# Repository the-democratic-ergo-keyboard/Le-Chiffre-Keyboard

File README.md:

# Le Chiffre (ironically, "the number" in French)
The purpose of the board is to provide a platform for MX and Choc ergo (Alps support too!) in one package for when ones wrists need a break. The board supports an RGB LED strip with DI on port F0. The board is also fitted with support for run-of-the-mill .91" OLED and EC11 rotary encoder.

Great thanks goes to Jake at P3D for really making the case amazing and open sourcing his work. Check him out at P3Dstore.com

Firmware for the keyboard is available here: https://github.com/qmk/qmk_firmware/tree/master/keyboards/tominabox1/le_chiffre

This project is open sourced with the GPL-3.0 license. The license conditionally allows for commercial use, modification, distribution, patent, and private use. Please take note of the license conditions before utilizing this project. 

## PCB

# Fab files
If you just want to order PCBs, just grab these files and send them to your fab house. The pos and bom for jlcpcb are already included as well

[PCB](KiCad/Le%20Chiffre%20v2/production/gerber.zip)

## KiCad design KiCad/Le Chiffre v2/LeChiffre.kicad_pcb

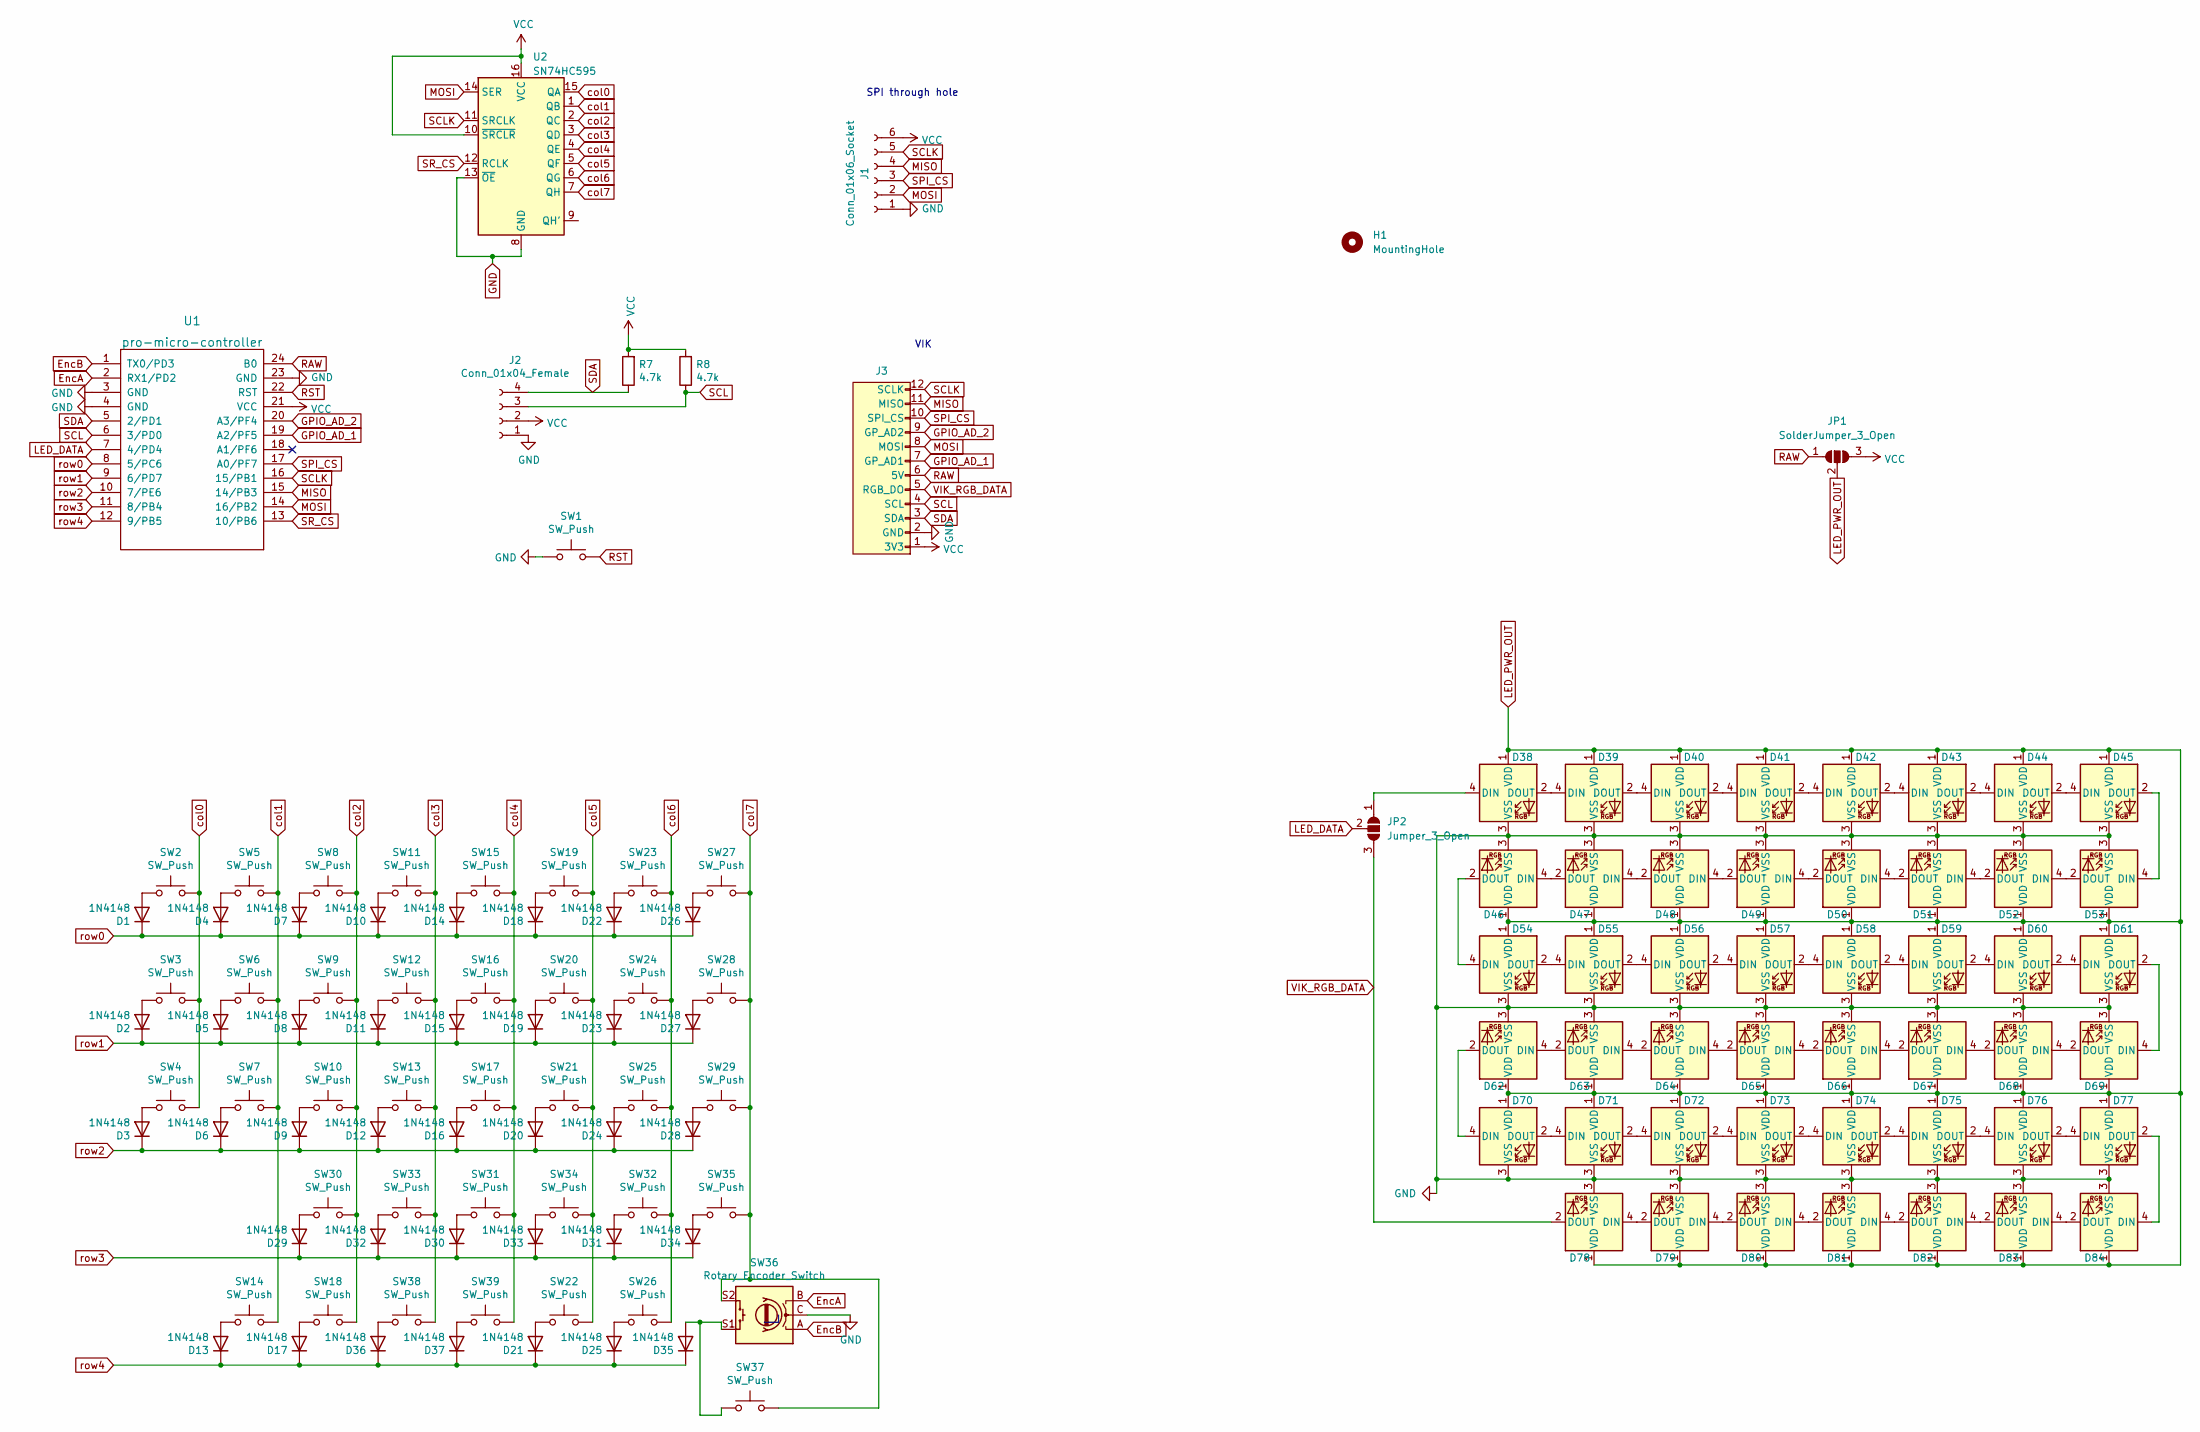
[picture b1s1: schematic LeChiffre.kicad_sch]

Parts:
D1, D2, D3, D4, D5, D6, D7, D8, D9, D10, D11, D12, D13, D14, D15, D16, D17, D18, D19, D20, D21, D22, D23, D24, D25, D26, D27, D28, D29, D30, D31, D32, D33, D34, D35, D36, D37: 1N4148; D_SOD123; LCSC C909967
D38, D39, D40, D41, D42, D43, D44, D45, D46, D47, D48, D49, D50, D51, D52, D53, D54, D55, D56, D57, D58, D59, D60, D61, D62, D63, D64, D65, D66, D67, D68, D69, D70, D71, D72, D73, D74, D75, D76, D77, D78, D79, D80, D81, D82, D83, D84: SK6803_MINI-E; SK6803-MINI-E; LCSC C5242955
H1: MountingHole; TPSensorModule
J1: Conn_01x06_Socket; PinHeader_1x06_P2.54mm_Vertical
J2: Conn_01x04_Female; PinSocket_1x04_P2.54mm_Vertical
J3: vik-keyboard-connector-horizontal; LCSC C479750
JP1: SolderJumper_3_Open; SolderJumper-3_P1.3mm_Open_RoundedPad1.0x1.5mm
JP2: Jumper_3_Open; SolderJumper-3_P1.3mm_Open_RoundedPad1.0x1.5mm
R7, R8: 4.7k; R_0805; LCSC C269746
SW1: SW_Push; SW_SPST_TL3342
SW2, SW3, SW4, SW5, SW6, SW7, SW8, SW9, SW10, SW11, SW12, SW13, SW14, SW15, SW16, SW17, SW18, SW19, SW20, SW21, SW22, SW23, SW24, SW25, SW26, SW27, SW28, SW29, SW30, SW31, SW32, SW33, SW34, SW35, SW37, SW38, SW39: SW_Push; MX-Alps-Choc-1U-NoLED
SW36: Rotary_Encoder_Switch; RotaryEncoder_Alps_EC12E-Switch_Vertical_H20mm_CircularMoun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
U1: pro-micro-controller
U2: SN74HC595; SOIC-16_3.9x9.9mm_P1.27mm; LCSC C94270

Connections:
EncA: SW36.B, U1.2 (RX1/PD2)
EncB: SW36.A, U1.1 (TX0/PD3)
GND: D38.3 (VSS), D39.3 (VSS), D40.3 (VSS), D41.3 (VSS), D42.3 (VSS), D43.3 (VSS), D44.3 (VSS), D45.3 (VSS), D46.3 (VSS), D47.3 (VSS), D48.3 (VSS), D49.3 (VSS), D50.3 (VSS), D51.3 (VSS), D52.3 (VSS), D53.3 (VSS), D54.3 (VSS), D55.3 (VSS), D56.3 (VSS), D57.3 (VSS), D58.3 (VSS), D59.3 (VSS), D60.3 (VSS), D61.3 (VSS), D62.3 (VSS), D63.3 (VSS), D64.3 (VSS), D65.3 (VSS), D66.3 (VSS), D67.3 (VSS), D68.3 (VSS), D69.3 (VSS), D70.3 (VSS), D71.3 (VSS), D72.3 (VSS), D73.3 (VSS), D74.3 (VSS), D75.3 (VSS), D76.3 (VSS), D77.3 (VSS), D78.3 (VSS), D79.3 (VSS), D80.3 (VSS), D81.3 (VSS), D82.3 (VSS), D83.3 (VSS), D84.3 (VSS), J1.1, J2.1, J3.2 (GND), SW1.1, SW36.C, U1.3 (GND), U1.4 (GND), U1.23 (GND), U2.8 (GND), U2.13 (~OE)
GPIO_AD_1: J3.7 (GP_AD1), U1.19 (A2/PF5)
GPIO_AD_2: J3.9 (GP_AD2), U1.20 (A3/PF4)
LED_DATA: JP2.2 (C), U1.7 (4/PD4)
LED_PWR_OUT: D38.1 (VDD), D39.1 (VDD), D40.1 (VDD), D41.1 (VDD), D42.1 (VDD), D43.1 (VDD), D44.1 (VDD), D45.1 (VDD), D46.1 (VDD), D47.1 (VDD), D48.1 (VDD), D49.1 (VDD), D50.1 (VDD), D51.1 (VDD), D52.1 (VDD), D53.1 (VDD), D54.1 (VDD), D55.1 (VDD), D56.1 (VDD), D57.1 (VDD), D58.1 (VDD), D59.1 (VDD), D60.1 (VDD), D61.1 (VDD), D62.1 (VDD), D63.1 (VDD), D64.1 (VDD), D65.1 (VDD), D66.1 (VDD), D67.1 (VDD), D68.1 (VDD), D69.1 (VDD), D70.1 (VDD), D71.1 (VDD), D72.1 (VDD), D73.1 (VDD), D74.1 (VDD), D75.1 (VDD), D76.1 (VDD), D77.1 (VDD), D78.1 (VDD), D79.1 (VDD), D80.1 (VDD), D81.1 (VDD), D82.1 (VDD), D83.1 (VDD), D84.1 (VDD), JP1.2 (C)
MISO: J1.4, J3.11 (MISO), U1.15 (14/PB3)
MOSI: J1.2, J3.8 (MOSI), U1.14 (16/PB2), U2.14 (SER)
unnamed: D1.2 (A), SW2.1
unnamed: D2.2 (A), SW3.1
unnamed: D3.2 (A), SW4.1
unnamed: D4.2 (A), SW5.1
unnamed: D5.2 (A), SW6.1
unnamed: D6.2 (A), SW7.1
unnamed: D7.2 (A), SW8.1
unnamed: D8.2 (A), SW9.1
unnamed: D9.2 (A), SW10.1
unnamed: D10.2 (A), SW11.1
unnamed: D11.2 (A), SW12.1
unnamed: D12.2 (A), SW13.1
unnamed: D13.2 (A), SW14.1
unnamed: D14.2 (A), SW15.1
unnamed: D15.2 (A), SW16.1
unnamed: D16.2 (A), SW17.1
unnamed: D17.2 (A), SW18.1
unnamed: D18.2 (A), SW19.1
unnamed: D19.2 (A), SW20.1
unnamed: D20.2 (A), SW21.1
unnamed: D21.2 (A), SW22.1
unnamed: D22.2 (A), SW23.1
unnamed: D23.2 (A), SW24.1
unnamed: D24.2 (A), SW25.1
unnamed: D25.2 (A), SW26.1
unnamed: D26.2 (A), SW27.1
unnamed: D27.2 (A), SW28.1
unnamed: D28.2 (A), SW29.1
unnamed: D29.2 (A), SW30.1
unnamed: D30.2 (A), SW31.1
unnamed: D31.2 (A), SW32.1
unnamed: D32.2 (A), SW33.1
unnamed: D33.2 (A), SW34.1
unnamed: D34.2 (A), SW35.1
unnamed: D35.2 (A), SW36.S1, SW37.1
unnamed: D36.2 (A), SW38.1
unnamed: D37.2 (A), SW39.1
unnamed: D38.4 (DIN), JP2.1 (A)
unnamed: D38.2 (DOUT), D39.4 (DIN)
unnamed: D39.2 (DOUT), D40.4 (DIN)
unnamed: D40.2 (DOUT), D41.4 (DIN)
unnamed: D41.2 (DOUT), D42.4 (DIN)
unnamed: D42.2 (DOUT), D43.4 (DIN)
unnamed: D43.2 (DOUT), D44.4 (DIN)
unnamed: D44.2 (DOUT), D45.4 (DIN)
unnamed: D45.2 (DOUT), D53.4 (DIN)
unnamed: D46.4 (DIN), D47.2 (DOUT)
unnamed: D46.2 (DOUT), D54.4 (DIN)
unnamed: D47.4 (DIN), D48.2 (DOUT)
unnamed: D48.4 (DIN), D49.2 (DOUT)
unnamed: D49.4 (DIN), D50.2 (DOUT)
unnamed: D50.4 (DIN), D51.2 (DOUT)
unnamed: D51.4 (DIN), D52.2 (DOUT)
unnamed: D52.4 (DIN), D53.2 (DOUT)
unnamed: D54.2 (DOUT), D55.4 (DIN)
unnamed: D55.2 (DOUT), D56.4 (DIN)
unnamed: D56.2 (DOUT), D57.4 (DIN)
unnamed: D57.2 (DOUT), D58.4 (DIN)
unnamed: D58.2 (DOUT), D59.4 (DIN)
unnamed: D59.2 (DOUT), D60.4 (DIN)
unnamed: D60.2 (DOUT), D61.4 (DIN)
unnamed: D61.2 (DOUT), D69.4 (DIN)
unnamed: D62.4 (DIN), D63.2 (DOUT)
unnamed: D62.2 (DOUT), D70.4 (DIN)
unnamed: D63.4 (DIN), D64.2 (DOUT)
unnamed: D64.4 (DIN), D65.2 (DOUT)
unnamed: D65.4 (DIN), D66.2 (DOUT)
unnamed: D66.4 (DIN), D67.2 (DOUT)
unnamed: D67.4 (DIN), D68.2 (DOUT)
unnamed: D68.4 (DIN), D69.2 (DOUT)
unnamed: D70.2 (DOUT), D71.4 (DIN)
unnamed: D71.2 (DOUT), D72.4 (DIN)
unnamed: D72.2 (DOUT), D73.4 (DIN)
unnamed: D73.2 (DOUT), D74.4 (DIN)
unnamed: D74.2 (DOUT), D75.4 (DIN)
unnamed: D75.2 (DOUT), D76.4 (DIN)
unnamed: D76.2 (DOUT), D77.4 (DIN)
unnamed: D77.2 (DOUT), D84.4 (DIN)
unnamed: D78.4 (DIN), D79.2 (DOUT)
unnamed: D79.4 (DIN), D80.2 (DOUT)
unnamed: D80.4 (DIN), D81.2 (DOUT)
unnamed: D81.4 (DIN), D82.2 (DOUT)
unnamed: D82.4 (DIN), D83.2 (DOUT)
unnamed: D83.4 (DIN), D84.2 (DOUT)
RAW: J3.6 (5V), JP1.1 (A), U1.24 (B0)
RST: SW1.2, U1.22 (RST)
SCL: J2.3, J3.4 (SCL), R8.1, U1.6 (3/PD0)
SCLK: J1.5, J3.12 (SCLK), U1.16 (15/PB1), U2.11 (SRCLK)
SDA: J2.4, J3.3 (SDA), R7.1, U1.5 (2/PD1)
SPI_CS: J1.3, J3.10 (SPI_CS), U1.17 (A0/PF7)
SR_CS: U1.13 (10/PB6), U2.12 (RCLK)
VCC: J1.6, J2.2, J3.1 (3V3), JP1.3 (B), R7.2, R8.2, U1.21 (VCC), U2.10 (~SRCLR), U2.16 (VCC)
VIK_RGB_DATA: D78.2 (DOUT), J3.5 (RGB_DO), JP2.3 (B)
col0: SW2.2, SW3.2, SW4.2, U2.15 (QA)
col1: SW5.2, SW6.2, SW7.2, SW14.2, U2.1 (QB)
col2: SW8.2, SW9.2, SW10.2, SW18.2, SW30.2, U2.2 (QC)
col3: SW11.2, SW12.2, SW13.2, SW33.2, SW38.2, U2.3 (QD)
col4: SW15.2, SW16.2, SW17.2, SW31.2, SW39.2, U2.4 (QE)
col5: SW19.2, SW20.2, SW21.2, SW22.2, SW34.2, U2.5 (QF)
col6: SW23.2, SW24.2, SW25.2, SW26.2, SW32.2, U2.6 (QG)
col7: SW27.2, SW28.2, SW29.2, SW35.2, SW36.S2, SW37.2, U2.7 (QH)
row0: D1.1 (K), D4.1 (K), D7.1 (K), D10.1 (K), D14.1 (K), D18.1 (K), D22.1 (K), D26.1 (K), U1.8 (5/PC6)
row1: D2.1 (K), D5.1 (K), D8.1 (K), D11.1 (K), D15.1 (K), D19.1 (K), D23.1 (K), D27.1 (K), U1.9 (6/PD7)
row2: D3.1 (K), D6.1 (K), D9.1 (K), D12.1 (K), D16.1 (K), D20.1 (K), D24.1 (K), D28.1 (K), U1.10 (7/PE6)
row3: D29.1 (K), D30.1 (K), D31.1 (K), D32.1 (K), D33.1 (K), D34.1 (K), U1.11 (8/PB4)
row4: D13.1 (K), D17.1 (K), D21.1 (K), D25.1 (K), D35.1 (K), D36.1 (K), D37.1 (K), U1.12 (9/PB5)

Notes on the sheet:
SPI through hole
VIK

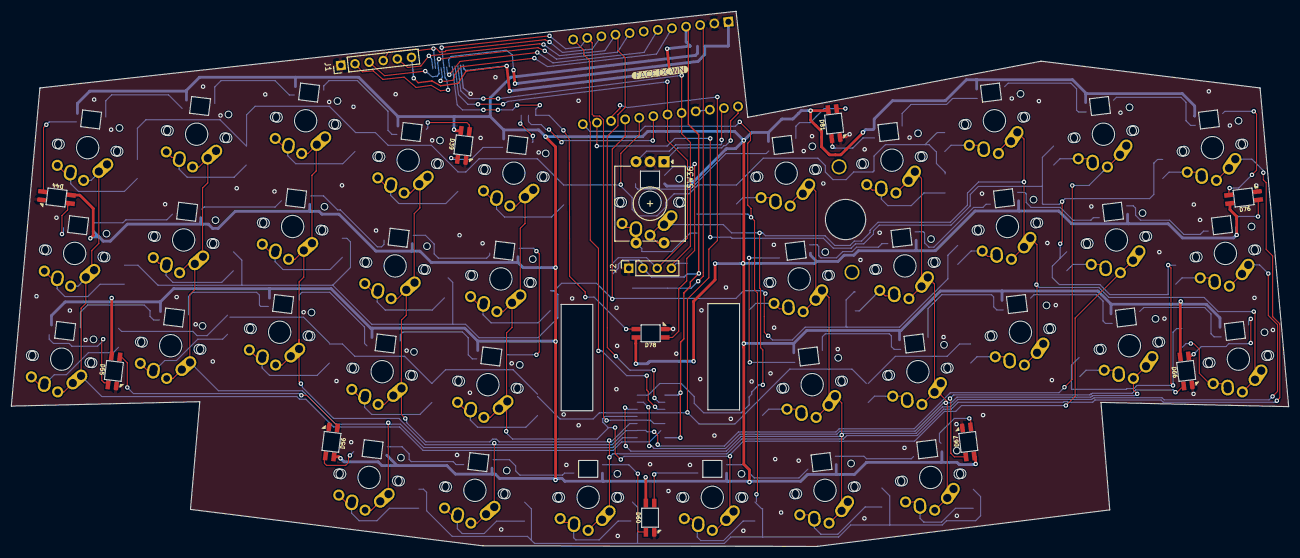
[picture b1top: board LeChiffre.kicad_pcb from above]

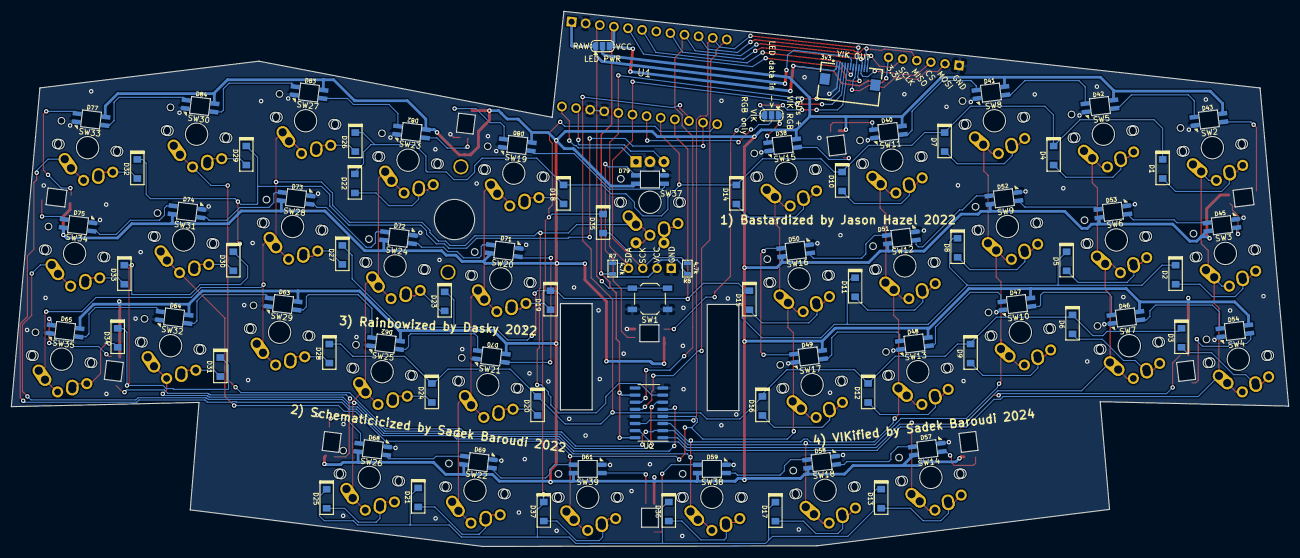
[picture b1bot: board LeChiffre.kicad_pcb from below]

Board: 2 copper layers, 228.3 x 95.6 mm, 134 parts (82 on the bottom side), 115 nets.

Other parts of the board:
kibuzzard-6397B74C: G***; kibuzzard-6397B74C

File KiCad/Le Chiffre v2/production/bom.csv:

Designator,Footprint,Quantity,Value,LCSC Part #
"D1, D10, D11, D12, D13, D14, D15, D16, D17, D18, D19, D2, D20, D21, D22, D23, D24, D25, D26, D27, D28, D29, D3, D30, D31, D32, D33, D34, D35, D36, D37, D4, D5, D6, D7, D8, D9",D_SOD123,37,1N4148,C909967
"D38, D39, D40, D41, D42, D43, D44, D45, D46, D47, D48, D49, D50, D51, D52, D53, D54, D55, D56, D57, D58, D59, D60, D61, D62, D63, D64, D65, D66, D67, D68, D69, D70, D71, D72, D73, D74, D75, D76, D77, D78, D79, D80, D81, D82, D83, D84",SK6803-MINI-E,47,SK6803_MINI-E,C5242955
H1,TPSensorModule,1,MountingHole,
J1,PinHeader_1x06_P2.54mm_Vertical,1,Conn_01x06_Socket,
J2,PinSocket_1x04_P2.54mm_Vertical,1,Conn_01x04_Female,
J3,vik-keyboard-connector-horizontal,1,~,C479750
JP1,SolderJumper-3_P1.3mm_Open_RoundedPad1.0x1.5mm,1,SolderJumper_3_Open,
JP2,SolderJumper-3_P1.3mm_Open_RoundedPad1.0x1.5mm,1,Jumper_3_Open,
"R7, R8",R_0805,2,4.7k,C269746
SW1,SW_SPST_TL3342,1,SW_Push,
"SW10, SW11, SW12, SW13, SW14, SW15, SW16, SW17, SW18, SW19, SW2, SW20, SW21, SW22, SW23, SW24, SW25, SW26, SW27, SW28, SW29, SW3, SW30, SW31, SW32, SW33, SW34, SW35, SW37, SW38, SW39, SW4, SW5, SW6, SW7, SW8, SW9",MX-Alps-Choc-1U-NoLED,37,SW_Push,
SW36,RotaryEncoder_Alps_EC12E-Switch_Vertical_H20mm_CircularMountingHoles,1,Rotary_Encoder_Switch,
U1,pro-micro-controller,1,pro-micro-controller,
U2,SOIC-16_3.9x9.9mm_P1.27mm,1,SN74HC595,C94270

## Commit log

2022-12-14 swapped to mcu daughterboard for no good reason
2022-12-14 cleanup tracks and vias
2022-12-14 forgot to save
2022-12-16 Schematics, key additions, changed shift registers, rerouting, and more, see changelog.md
2022-12-22 rainbow mode
2022-12-22 Added PCBA for Dasky's changes
2022-12-23 Splay
2022-12-23 Auto Render PCB
2022-12-23 Add changes to change log
2022-12-23 Updated gerbers per AlaaSaadAbdo's last PR
2022-12-26 fixed readme to reflect the current state of pcb
2023-01-04 silkscreen art
2023-01-10 Update gallery (automated)
2023-01-10 adding bottom render
2023-01-18 fix: Left pinky per key RGB position
2023-03-04 bom's long delayed forehead
2023-03-04 tidy up old fab stuff for now
2023-03-04 fixup boms edgecut edits
2023-03-04 add boms bom to changelog
2024-02-28 added vik support, and extra spi through holes
2024-03-01 led data no longer bridged by default, and fixed silk for vikification message
2024-03-04 added better VIK cable openings
2024-03-05 added trackpoint mounting support
2024-04-01 fixed diode orientation to work with shift register
